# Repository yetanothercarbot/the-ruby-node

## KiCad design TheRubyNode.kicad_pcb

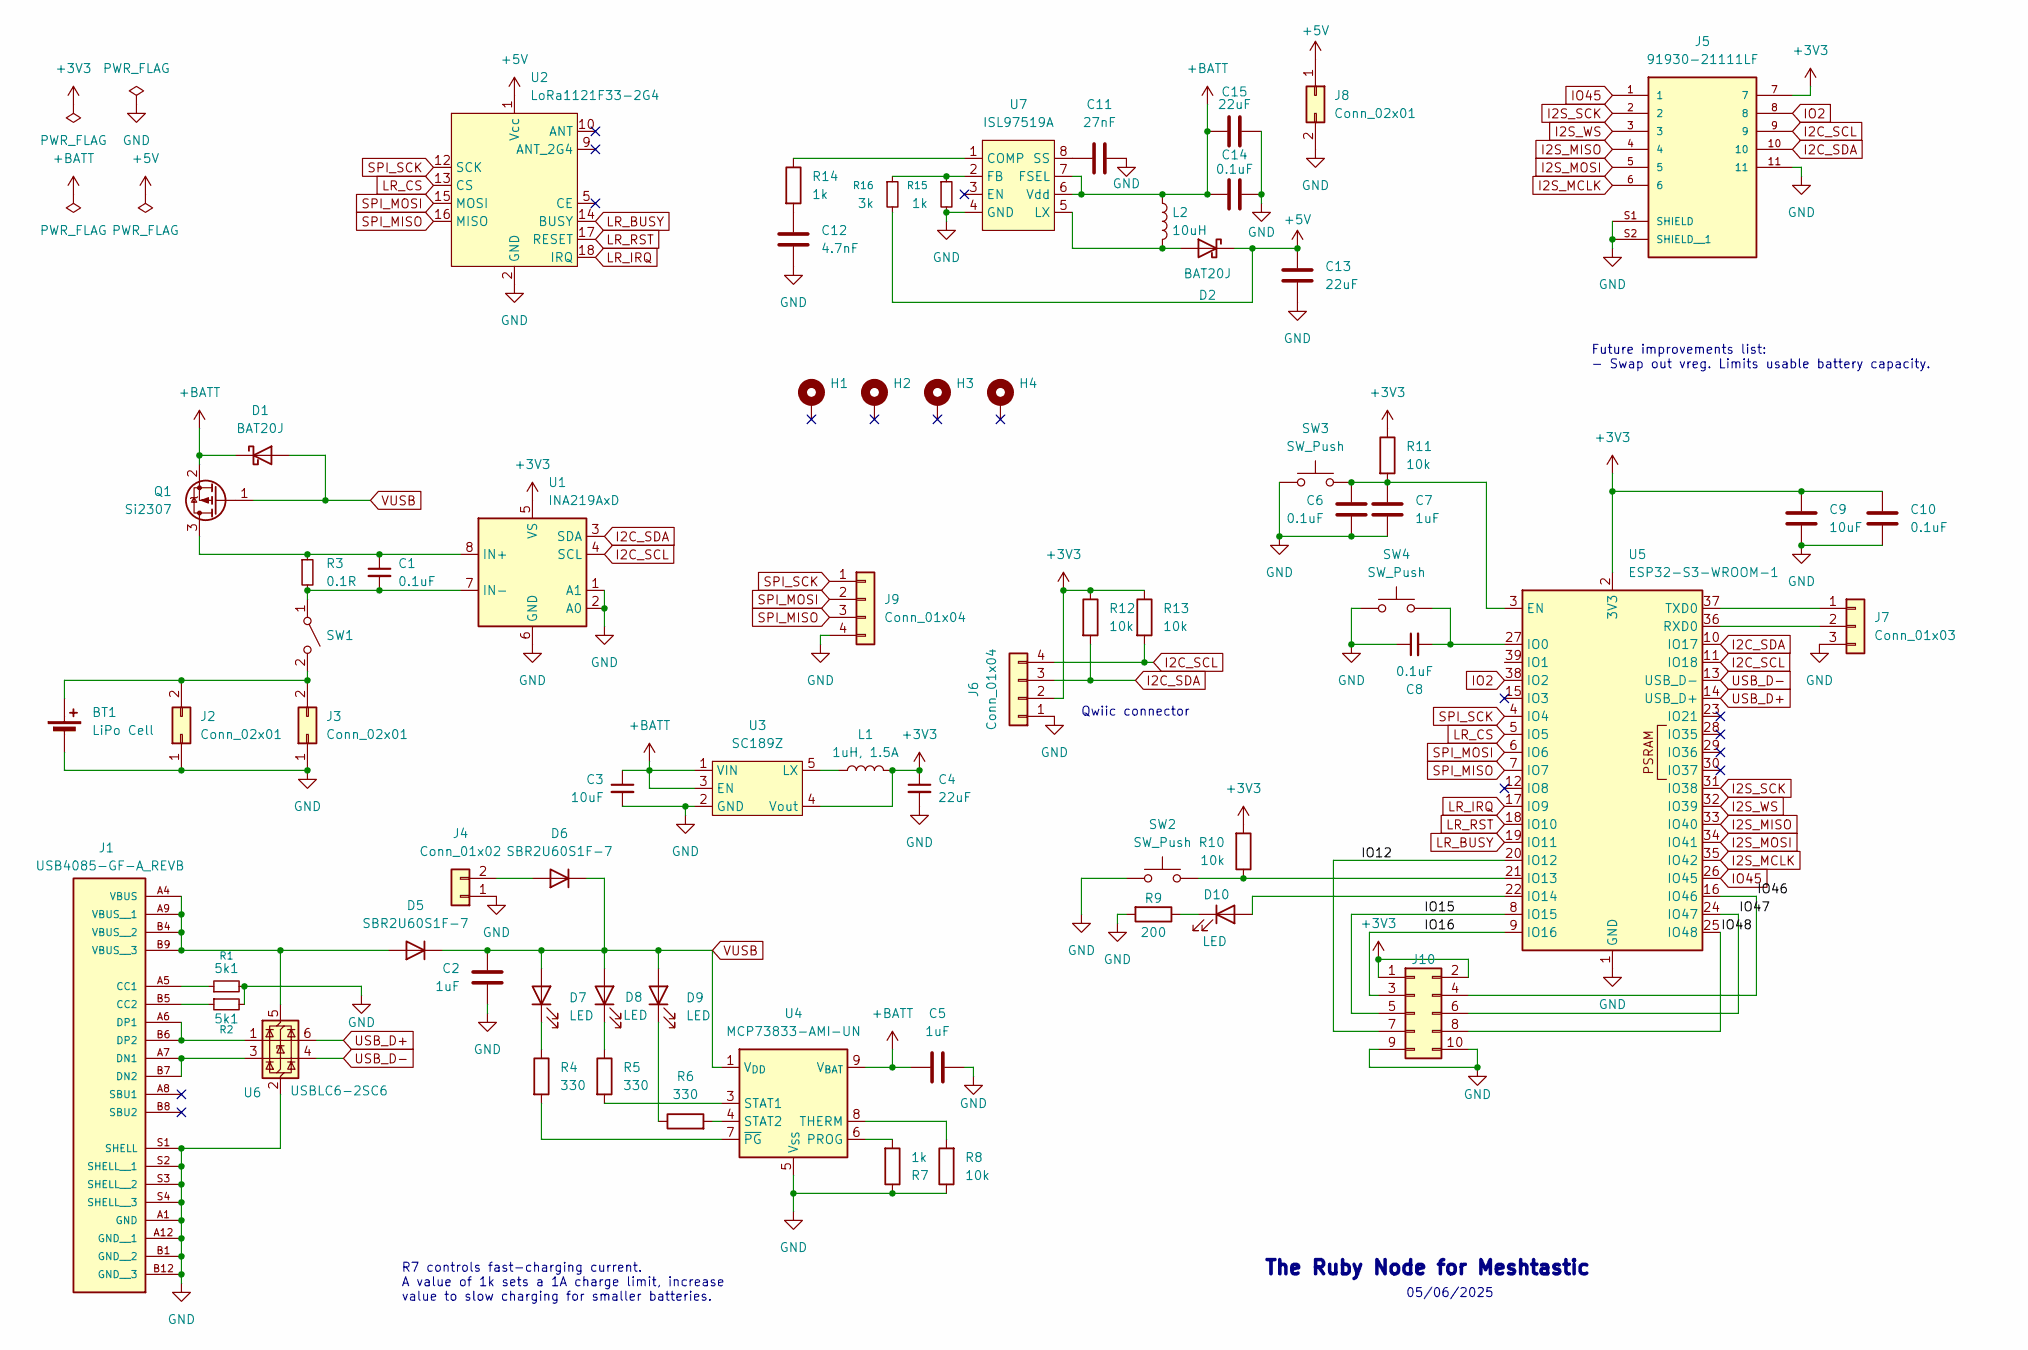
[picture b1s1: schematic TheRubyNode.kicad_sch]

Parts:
BT1: LiPo Cell; BatteryHolder_Keystone_1042_1x18650
C1, C6, C8, C10, C14: 0.1uF; C_0805_2012Metric_Pad1.18x1.45mm_HandSolder
C2, C5, C7: 1uF; C_0805_2012Metric_Pad1.18x1.45mm_HandSolder
C3, C9: 10uF; C_0805_2012Metric_Pad1.18x1.45mm_HandSolder
C4, C13, C15: 22uF; C_0805_2012Metric_Pad1.18x1.45mm_HandSolder
C11: 27nF; C_0805_2012Metric_Pad1.18x1.45mm_HandSolder
C12: 4.7nF; C_0805_2012Metric_Pad1.18x1.45mm_HandSolder
D1, D2: BAT20J; D_SOD-323_HandSoldering
D5, D6: SBR2U60S1F-7; D_SOD-123F
D7, D8, D9: LED; LED_1206_3216Metric_Pad1.42x1.75mm_HandSolder
D10: LED; LED_PLCC_2835_Handsoldering
H1, H2, H3, H4: MountingHole_Pad; MountingHole_3.2mm_M3_Pad
J1: USB4085-GF-A_REVB; GCT_USB4085-GF-A_REVB; PARTREV B
J2, J3: Conn_02x01; JST_PH_S2B-PH-SM4-TB_1x02-1MP_P2.00mm_Horizontal
J4: Conn_01x02; JST_PH_S2B-PH-SM4-TB_1x02-1MP_P2.00mm_Horizontal
J5: 91930-21111LF; AMPHENOL_91930-21111LF; PARTREV AN
J6: Conn_01x04; JST_SH_BM04B-SRSS-TB_1x04-1MP_P1.00mm_Vertical
J7: Conn_01x03; PinHeader_1x03_P2.54mm_Vertical
J8: Conn_02x01; JST_PH_B2B-PH-SM4-TB_1x02-1MP_P2.00mm_Vertical
J9: Conn_01x04; PinHeader_1x04_P2.54mm_Vertical
J10: Conn_02x05_Odd_Even; PinSocket_2x05_P2.54mm_Vertical
L1: 1uH, 1.5A; L_0805_2012Metric_Pad1.05x1.20mm_HandSolder
L2: 10uH; Inductor_2424
Q1: Si2307; SOT-23
R1, R2: 5k1; R_0805_2012Metric_Pad1.20x1.40mm_HandSolder
R3: 0.1R; R_2512_6332Metric_Pad1.40x3.35mm_HandSolder
R4, R5, R6: 330; R_0805_2012Metric_Pad1.20x1.40mm_HandSolder
R7, R14, R15: 1k; R_0805_2012Metric_Pad1.20x1.40mm_HandSolder
R8, R10, R11, R12, R13: 10k; R_0805_2012Metric_Pad1.20x1.40mm_HandSolder
R9: 200; R_0805_2012Metric_Pad1.20x1.40mm_HandSolder
R16: 3k; R_0805_2012Metric_Pad1.20x1.40mm_HandSolder
SW1: SW_SPST; JST_PH_B2B-PH-SM4-TB_1x02-1MP_P2.00mm_Vertical
SW2: SW_Push; JST_PH_B2B-PH-SM4-TB_1x02-1MP_P2.00mm_Vertical
SW3, SW4: SW_Push; SW_SPST_PTS645
U1: INA219AxD; SOIC-8_3.9x4.9mm_P1.27mm
U2: LoRa1121F33-2G4; LoRa1121F33
U3: SC189Z; SOT-23-5_HandSoldering
U4: MCP73833-AMI-UN; MSOP-10_3x3mm_P0.5mm
U5: ESP32-S3-WROOM-1; ESP32-S3-WROOM-1U
U6: USBLC6-2SC6; SOT-23-6
U7: ISL97519A; MSOP-8_3x3mm_P0.65mm

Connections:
+3V3: C4.1, C9.1, C10.1, J5.7, J6.2, J10.1, J10.2, L1.2, R10.2, R11.1, R12.1, R13.1, U1.5 (VS), U3.4 (Vout), U5.2 (3V3)
+5V: C13.1, D2.1 (K), J8.1, R16.2, U2.1 (Vcc)
+BATT: C3.1, C5.1, C14.1, C15.1, D1.1 (K), L2.1, Q1.2 (S), U3.1 (VIN), U3.3 (EN), U4.9 (V_{BAT}), U4.10 (V_{BAT}), U7.6 (Vdd), U7.7 (FSEL)
/IO12: J10.7, U5.20 (IO12)
/IO15: J10.5, U5.8 (IO15)
/IO16: J10.3, U5.9 (IO16)
/IO46: J10.4, U5.16 (IO46)
/IO47: J10.6, U5.24 (IO47)
/IO48: J10.8, U5.25 (IO48)
GND: BT1.2 (-), C2.2, C3.2, C4.2, C5.2, C6.2, C7.1, C8.1, C9.2, C10.2, C11.2, C12.2, C13.2, C14.2, C15.2, J1.A1 (GND), J1.A12 (GND__1), J1.B1 (GND__2), J1.B12 (GND__3), J1.S1 (SHELL), J1.S2 (SHELL__1), J1.S3 (SHELL__2), J1.S4 (SHELL__3), J2.1, J3.1, J4.1, J5.11, J5.S1 (SHIELD), J5.S2 (SHIELD__1), J6.1, J7.3, J8.2, J9.4, J10.9, J10.10, R1.2, R2.2, R7.1, R8.1, R9.2, R15.2, SW2.1, SW3.1, SW4.1, U1.1 (A1), U1.2 (A0), U1.6 (GND), U2.2 (GND), U2.3 (GND), U2.4 (GND), U2.6 (GND), U2.7 (GND), U2.8 (GND), U2.11 (GND), U2.19 (GND), U2.20 (GND), U3.2 (GND), U4.5 (V_{SS}), U5.1 (GND), U5.40 (GND), U5.41 (GND), U6.2 (GND), U7.4 (GND)
I2C_SCL: J5.9, J6.4, R13.2, U1.4 (SCL), U5.11 (IO18)
I2C_SDA: J5.10, J6.3, R12.2, U1.3 (SDA), U5.10 (IO17)
I2S_MCLK: J5.6, U5.35 (IO42)
I2S_MISO: J5.4, U5.33 (IO40)
I2S_MOSI: J5.5, U5.34 (IO41)
I2S_SCK: J5.2, U5.31 (IO38)
I2S_WS: J5.3, U5.32 (IO39)
IO2: J5.8, U5.38 (IO2)
IO45: J5.1, U5.26 (IO45)
LR_BUSY: U2.14 (BUSY), U5.19 (IO11)
LR_CS: U2.13 (CS), U5.5 (IO5)
LR_IRQ: U2.18 (IRQ), U5.17 (IO9)
LR_RST: U2.17 (RESET), U5.18 (IO10)
unnamed: BT1.1 (+), J2.2, J3.2, SW1.2 (B)
unnamed: C12.1, R14.2
unnamed: D2.2 (A), L2.2, U7.5 (LX)
unnamed: D5.2 (A), J1.A4 (VBUS), J1.A9 (VBUS__1), J1.B4 (VBUS__2), J1.B9 (VBUS__3), U6.5 (VBUS)
unnamed: D6.2 (A), J4.2
unnamed: D7.1 (K), R4.1
unnamed: D8.1 (K), R5.1
unnamed: D9.1 (K), R6.1
unnamed: D10.2 (A), U5.22 (IO14)
unnamed: D10.1 (K), R9.1
unnamed: J1.A5 (CC1), R1.1
unnamed: J1.B5 (CC2), R2.1
unnamed: J1.A7 (DN1), J1.B7 (DN2), U6.3 (I/O2)
unnamed: J1.A6 (DP1), J1.B6 (DP2), U6.1 (I/O1)
unnamed: J7.1, U5.37 (TXD0)
unnamed: J7.2, U5.36 (RXD0)
unnamed: C1.1, Q1.3 (D), R3.1, U1.8 (IN+)
unnamed: C1.2, R3.2, SW1.1 (A), U1.7 (IN-)
unnamed: L1.1, U3.5 (LX)
unnamed: R7.2, U4.6 (PROG)
unnamed: R5.2, U4.3 (STAT1)
unnamed: R6.2, U4.4 (STAT2)
unnamed: R8.2, U4.8 (THERM)
unnamed: R4.2, U4.7 (~PG)
unnamed: C6.1, C7.2, R11.2, SW3.2, U5.3 (EN)
unnamed: C8.2, SW4.2, U5.27 (IO0)
unnamed: R10.1, SW2.2, U5.21 (IO13)
unnamed: R14.1, U7.1 (COMP)
unnamed: R15.1, R16.1, U7.2 (FB)
unnamed: C11.1, U7.8 (SS)
SPI_MISO: J9.3, U2.16 (MISO), U5.7 (IO7)
SPI_MOSI: J9.2, U2.15 (MOSI), U5.6 (IO6)
SPI_SCK: J9.1, U2.12 (SCK), U5.4 (IO4)
USB_D+: U5.14 (USB_D+), U6.6 (I/O1)
USB_D-: U5.13 (USB_D-), U6.4 (I/O2)
VUSB: C2.1, D1.2 (A), D5.1 (K), D6.1 (K), D7.2 (A), D8.2 (A), D9.2 (A), Q1.1 (G), U4.1 (V_{DD}), U4.2 (V_{DD})

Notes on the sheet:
The Ruby Node for Meshtastic
R7 controls fast-charging current. A value of 1k sets a 1A charge limit, increase value to slow charging for smaller batteries.
05/06/2025
Future improvements list: - Swap out vreg. Limits usable battery capacity.
Qwiic connector

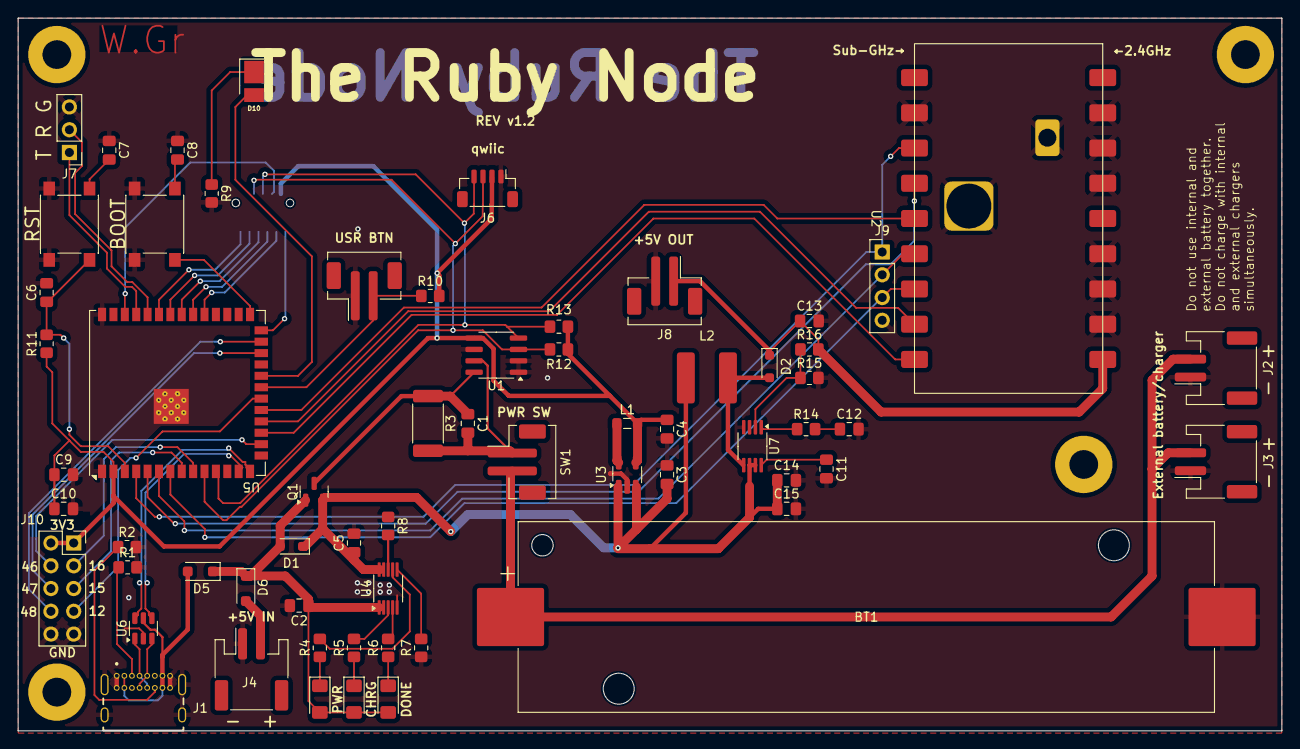
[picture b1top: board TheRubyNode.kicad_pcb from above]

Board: 2 copper layers, 141.0 x 79.5 mm, 68 parts (1 on the bottom side), 59 nets.

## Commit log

2025-06-11 Finish footprints, start of pcb
2025-06-12 Add PCB design
2025-06-13 PCB layout changes (rounded)
2025-06-13 Don't commit plots
2025-06-16 Finalise rev 1.0 of PCB
2025-06-22 Break out additional IOs
2025-06-22 Add pin labels
